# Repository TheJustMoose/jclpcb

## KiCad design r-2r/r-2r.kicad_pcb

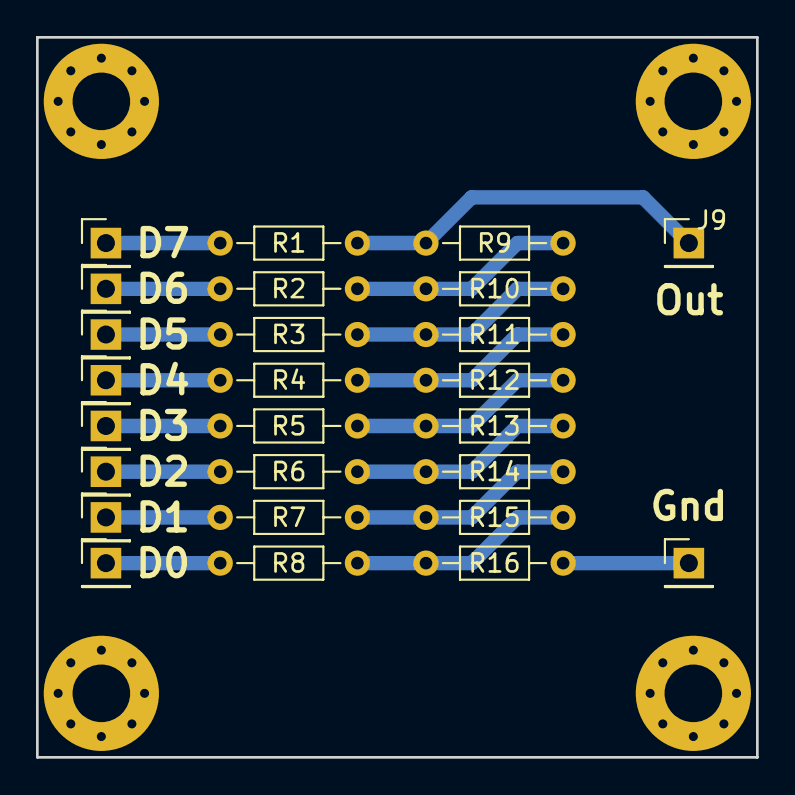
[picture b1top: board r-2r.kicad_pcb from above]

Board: 2 copper layers, 40.0 x 40.0 mm, 30 parts (0 on the bottom side), 17 nets.

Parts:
J1: D7; PinHeader_1x01_P2.54mm_Vertical
J2: D6; PinHeader_1x01_P2.54mm_Vertical
J3: D5; PinHeader_1x01_P2.54mm_Vertical
J4: D4; PinHeader_1x01_P2.54mm_Vertical
J5: D3; PinHeader_1x01_P2.54mm_Vertical
J6: D2; PinHeader_1x01_P2.54mm_Vertical
J7: D1; PinHeader_1x01_P2.54mm_Vertical
J8: D0; PinHeader_1x01_P2.54mm_Vertical
J9: Out; PinHeader_1x01_P2.54mm_Vertical
J10: Gnd; PinHeader_1x01_P2.54mm_Vertical
MH1, MH2, MH3, MH4: MountingHole; MountingHole_3.2mm_M3_Pad_Via
R1, R2, R3, R4, R5, R6, R7, R8, R16: 2k; R_Axial_DIN0204_L3.6mm_D1.6mm_P7.62mm_Horizontal
R9, R10, R11, R12, R13, R14, R15: 1k; R_Axial_DIN0204_L3.6mm_D1.6mm_P7.62mm_Horizontal

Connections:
GND: J10.1, R16.2
unnamed: J1.1, R1.2
unnamed: J2.1, R2.2
unnamed: J3.1, R3.2
unnamed: J4.1, R4.2
unnamed: J5.1, R5.2
unnamed: J6.1, R6.2
unnamed: J7.1, R7.2
unnamed: J8.1, R8.2
unnamed: J9.1, R1.1, R9.1
unnamed: R2.1, R9.2, R10.1
unnamed: R3.1, R10.2, R11.1
unnamed: R4.1, R11.2, R12.1
unnamed: R5.1, R12.2, R13.1
unnamed: R6.1, R13.2, R14.1
unnamed: R7.1, R14.2, R15.1
unnamed: R8.1, R15.2, R16.1

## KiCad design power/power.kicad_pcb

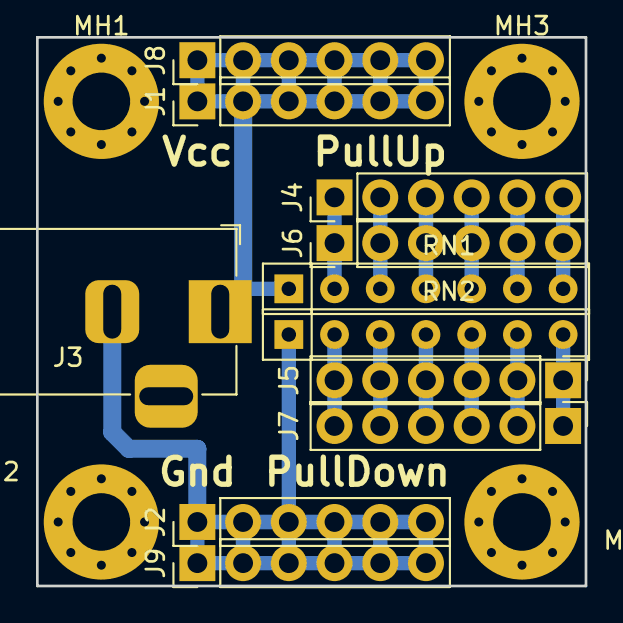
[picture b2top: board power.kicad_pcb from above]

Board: 2 copper layers, 30.5 x 30.5 mm, 15 parts (0 on the bottom side), 14 nets.

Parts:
J1, J2, J4, J5, J6, J7, J8, J9: Conn_01x06_Male; PinHeader_1x06_P2.54mm_Vertical_BigHoles
J3: Jack-DC; BarrelJack_Horizontal
MH1, MH2, MH3, MH4: MountingHole; MountingHole_3.2mm_M3_Pad_Via
RN1, RN2: R_Network06; R_Array_SIP7

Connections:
GND: J2.1, J2.2, J2.3, J2.4, J2.5, J2.6, J3.2, J9.1, J9.2, J9.3, J9.4, J9.5, J9.6, RN2.1
unnamed: J4.1, J6.1, RN1.2
unnamed: J4.2, J6.2, RN1.3
unnamed: J4.3, J6.3, RN1.4
unnamed: J4.4, J6.4, RN1.5
unnamed: J4.5, J6.5, RN1.6
unnamed: J4.6, J6.6, RN1.7
unnamed: J5.1, J7.1, RN2.7
unnamed: J5.2, J7.2, RN2.6
unnamed: J5.3, J7.3, RN2.5
unnamed: J5.4, J7.4, RN2.4
unnamed: J5.5, J7.5, RN2.3
unnamed: J5.6, J7.6, RN2.2
VCC: J1.1, J1.2, J1.3, J1.4, J1.5, J1.6, J3.1, J8.1, J8.2, J8.3, J8.4, J8.5, J8.6, RN1.1

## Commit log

2019-07-15 Pcb with power pins
2019-07-16 R-2R
2019-07-16 Ready
2019-07-16 R-2R pcb
2019-07-17 Add mounting holes
2019-07-23 Enlarge pcb to 40 x 40
2019-07-26 R-2R ready
